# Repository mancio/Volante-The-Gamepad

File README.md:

# Volante-The-Gamepad
The new revolutionary joystick for car and flight simulation games.

*(Design still in progress 😆)*

&nbsp;

*carbon 3d preview*

&nbsp;

*3d preview with classic ABS box*

&nbsp;

*prototype with home-made touch buttons*

&nbsp;

&nbsp;

*prototype with classic RC remote buttons*

### Software 
The code is written by using the famous libray ```Joystick.h```. You can find some sketches still in testing [here](https://github.com/mancio/Volante-The-Gamepad/tree/master/Volante%20sketch).
After some tests seem that only the ```JOYSTICK_TYPE_JOYSTICK``` configuration works. Unfortunately Microsoft stop to support the HID human interface and only the basic function works. Still no solution for force feedback and particular multiaxis joystick.... now the more complex gaming simulation devices have their own drivers. You don't need the basic plug and play driver. Please have a look for the [HID architecture](https://docs.microsoft.com/en-us/windows-hardware/drivers/hid/) to understand and maybe help 😵

### Hardware
The hardware include a joystick case, buttons, knobs, the [Arduino Pro Micro](https://www.sparkfun.com/products/12640) and the the shield to interface the Arduino with the gamepad hw. The button pad modules and the shield boards are designed with [KiCad](http://kicad-pcb.org/). You can find on [OSH Park](https://oshpark.com) the PCBs ready to print.
1. [First design - only push buttons](https://oshpark.com/shared_projects/Fl5pqxbd)
2. [Second design - esternal pull-up resistors](https://oshpark.com/shared_projects/2LW72doK)

### Directory structure
1. [ArduinoJoystickLibrary-master](https://github.com/mancio/Volante-The-Gamepad/tree/master/ArduinoJoystickLibrary-master) - the Joystick library written by [Matthew Heironimus](https://github.com/MHeironimus)

2. [Fritzing](https://github.com/mancio/Volante-The-Gamepad/tree/master/Fritzing) - The Fritzing project with a prototype on breadbord. A small sketch to give a basic idea.

3. [Picture](https://github.com/mancio/Volante-The-Gamepad/tree/master/Picture) - some pictures for the Fritzing design project and the building process

4. [Volante sketch](https://github.com/mancio/Volante-The-Gamepad/tree/master/Volante%20sketch) - the code
   
   - [Volante](https://github.com/mancio/Volante-The-Gamepad/blob/master/Volante%20sketch/Volante/Volante.ino) - the main Arduino sketch. The sketch is design to be used with touch, capacitive and push buttons. The I/O pin can be in PULL-UP, PULL-DOWN or FLOAT configuration. 
      - touch button design: The PINs change to LOW when the finger or any not-hi-resistance organic object connect both the pad tracks. The finger and each resistor on the shield should be considered part of a voltage devider. Your dry skin should have an internal resistance of 2 MOhm so the resistors on the shield should be >= 10 MOhm. You can use [this](http://www.ohmslawcalculator.com/voltage-divider-calculator) voltage devider calculator to calculate the resistor value. The Arduino pin mosfets are LOW state when the input is about <= 2.5V. If you use a less conductive material to close the contacts of the pad maybe you will have to raise the resistance up to 20MOhm. Remeber that an high resistance voltage devider make the input *(dancing* 🎶 *)*. You could see the button blipping when you touch the button pad (only one contact or both). This effect is usualy caused by the power supply cord (I'm testing on a laptop). To reduce this effect you should a cercamic capacitor between the input and the ground. The capacitor store a small charge when you press the button and release it very slowly due to the very high value resistors. This stop the flipping but introduce a small delay. You should try some caps between 100pF (101 value) - 100nF (104 value) until your find the best compromise for your application. I suggest 10nF (103 value) capacitor.
      
      [Here](https://www.tinkercad.com/things/0KRsWQPfhxv) Some experiments on ThinkerCad.
      
      &nbsp;
      
      *touch button pad (the resistors are on the shield)* 
      &nbsp;
      
      - capacitive design: you can use the [TTP223](https://infusionsystems.com/support/TTP223.pdf) touch module as push button Normally LOW. The button switch on/off by using an internal timer that estimate the change of the capacitive charge during a fixed time slice. I suggest this configuration only for fast operation where is not required precision. The buttons are fast to trigger but sensible to external environment (high probability of fake positive) and the chip autoreset after few seconds (do not use as acceleretor button in a game)  
      
      &nbsp;
      
      *capacitive module* 
      &nbsp;
      
      - classic push button design: you can set up NO (normally open push button) using a pull-up configuration to reduce bouncing effects. When you push the button the pin will be GND. This is the most simple configuration, the button will be very reactive but harder to trigger (the most of NO push buttons are hard to click)
      
      &nbsp;
      
      *NO Momentary push button for RC* 
      &nbsp;

   - [test](https://github.com/mancio/Volante-The-Gamepad/blob/master/Volante%20sketch/test/test.ino) - Used to check the buttons assignment. 
   
      - int wiring[18] = Arduino pin in the IDE
      - int binding[18] = Buttons of joystick lib
      - String pull_mask[18] = pin state? High Low float (depending by the button type used)
      - analog_mask[18] = is analog? (for example pot is analog and push button is digital)
      
      Write the button structure with arrays here, execute the code and check in the table if the button binding is correct. If the binding satisfy your magic fingers copy this configuration to the main code ``Volante.ino``

5. [kicad](https://github.com/mancio/Volante-The-Gamepad/tree/master/kicad) - the Kicad scheme and PCB project.

   - [buttons_layout](https://github.com/mancio/Volante-The-Gamepad/tree/master/kicad/buttons_layout) - the blueprint of the gamepad case with RC push buttons
   
   - [buttons_layout_touch](https://github.com/mancio/Volante-The-Gamepad/tree/master/kicad/buttons_layout_touch) - the blueprint of the gamepad case with touch buttons
   
   - [lib](https://github.com/mancio/Volante-The-Gamepad/tree/master/kicad/lib) - kicad libraries of this project (include in kicad before open the project)
   
   - [shield](https://github.com/mancio/Volante-The-Gamepad/tree/master/kicad/shield) - firrst shield design only for capacitive and push buttons
   
      &nbsp;
      
      *First PCB printed by OSH Park* 
      &nbsp;
      
      &nbsp;
      
      *First PCB 3D view design by KiCad* 
      &nbsp;
   
   - [shield_touch](https://github.com/mancio/Volante-The-Gamepad/tree/master/kicad/shield_touch) - second shield design with extaernal pull-up resistor for push, capacitive and touch buttons.
   
      &nbsp;
      
      *Second PCB printed by OSH Park and assembled manually* 
      &nbsp;
      
      &nbsp;
      
      *Second PCB 3D view design by KiCad* 
      &nbsp;
   
   - [touch_button_fancy](https://github.com/mancio/Volante-The-Gamepad/tree/master/kicad/touch_button_fancy) - alternative push button PCB design
   
   - [touch_button_simple](https://github.com/mancio/Volante-The-Gamepad/tree/master/kicad/touch_button_simple) - main push button PCB design

6. [Assetto Corsa/Lotus GT Dream](https://github.com/mancio/Volante-The-Gamepad/tree/master/Assetto%20Corsa/Lotus%20GT%20Dream) - See *Cars for Assetto Corsa*

7. [Gamepad 3d design](https://github.com/mancio/Volante-The-Gamepad/tree/master/Gamepad%203d%20design) - 3d model of the gamepad Volante

      &nbsp;
      
      *3D rendering plastic box* 
      &nbsp;
   
### Game Setup

How to set up the Volante for a Awesome gaming experience

1. [Assetto corsa](https://www.assettocorsa.net/en/)

   &nbsp;
   
   *Main control configuration* 
   &nbsp;
   
   &nbsp;
   
   *Steering settings* 
   &nbsp;
   
### Cars for Assetto Corsa

To make the life easy to all the funs of the amazing game Assetto Corsa I decided to build my own cars (big tail and stick to the ground :red_car:). In the folder you find the game data and the blend file made with [blender](https://www.blender.org/)

1. [Lotus GT Dream](https://github.com/mancio/Volante-The-Gamepad/tree/master/Assetto%20Corsa/Lotus%20GT%20Dream)
   
### Facebook

You can find my project on Facebook on [Andrea Mancini's Machines](https://www.facebook.com/pg/mancio.tech/photos/?tab=album&album_id=2003051576403796)

### Conclusion
This project is focused to design a new kind of joystick that make pleasant the racing and flight simulation gaming experience.
The joystick will provide a slider linear potentiometer (throttle/brake), two knobs potentiometers (up/down - left/right) and 15 buttons
The innovation from the past consist in the _linear potentiometers_ that give the possibility to the player to perform absolutely precise movements.

#### Note
Don't worry if is not totally clear.... This project is still under development.

&nbsp;

#### Donation

Studying, designing and prototiping is expensive. If you believe in my project you can help me 😜 💲💲💲💲💲💲 😎

   - Bitcoin ```1KB6oxVrh5P6SbwFdtNHSG1rqPmdsaTaDV```

   - ETH ```0x7a5b81b2174748d6573a9ebf6b16d07c634c3e4f```

   - Litecoin ```LdVFaYbAsx9txhjVk1KURWvXqpVFDyT35k```

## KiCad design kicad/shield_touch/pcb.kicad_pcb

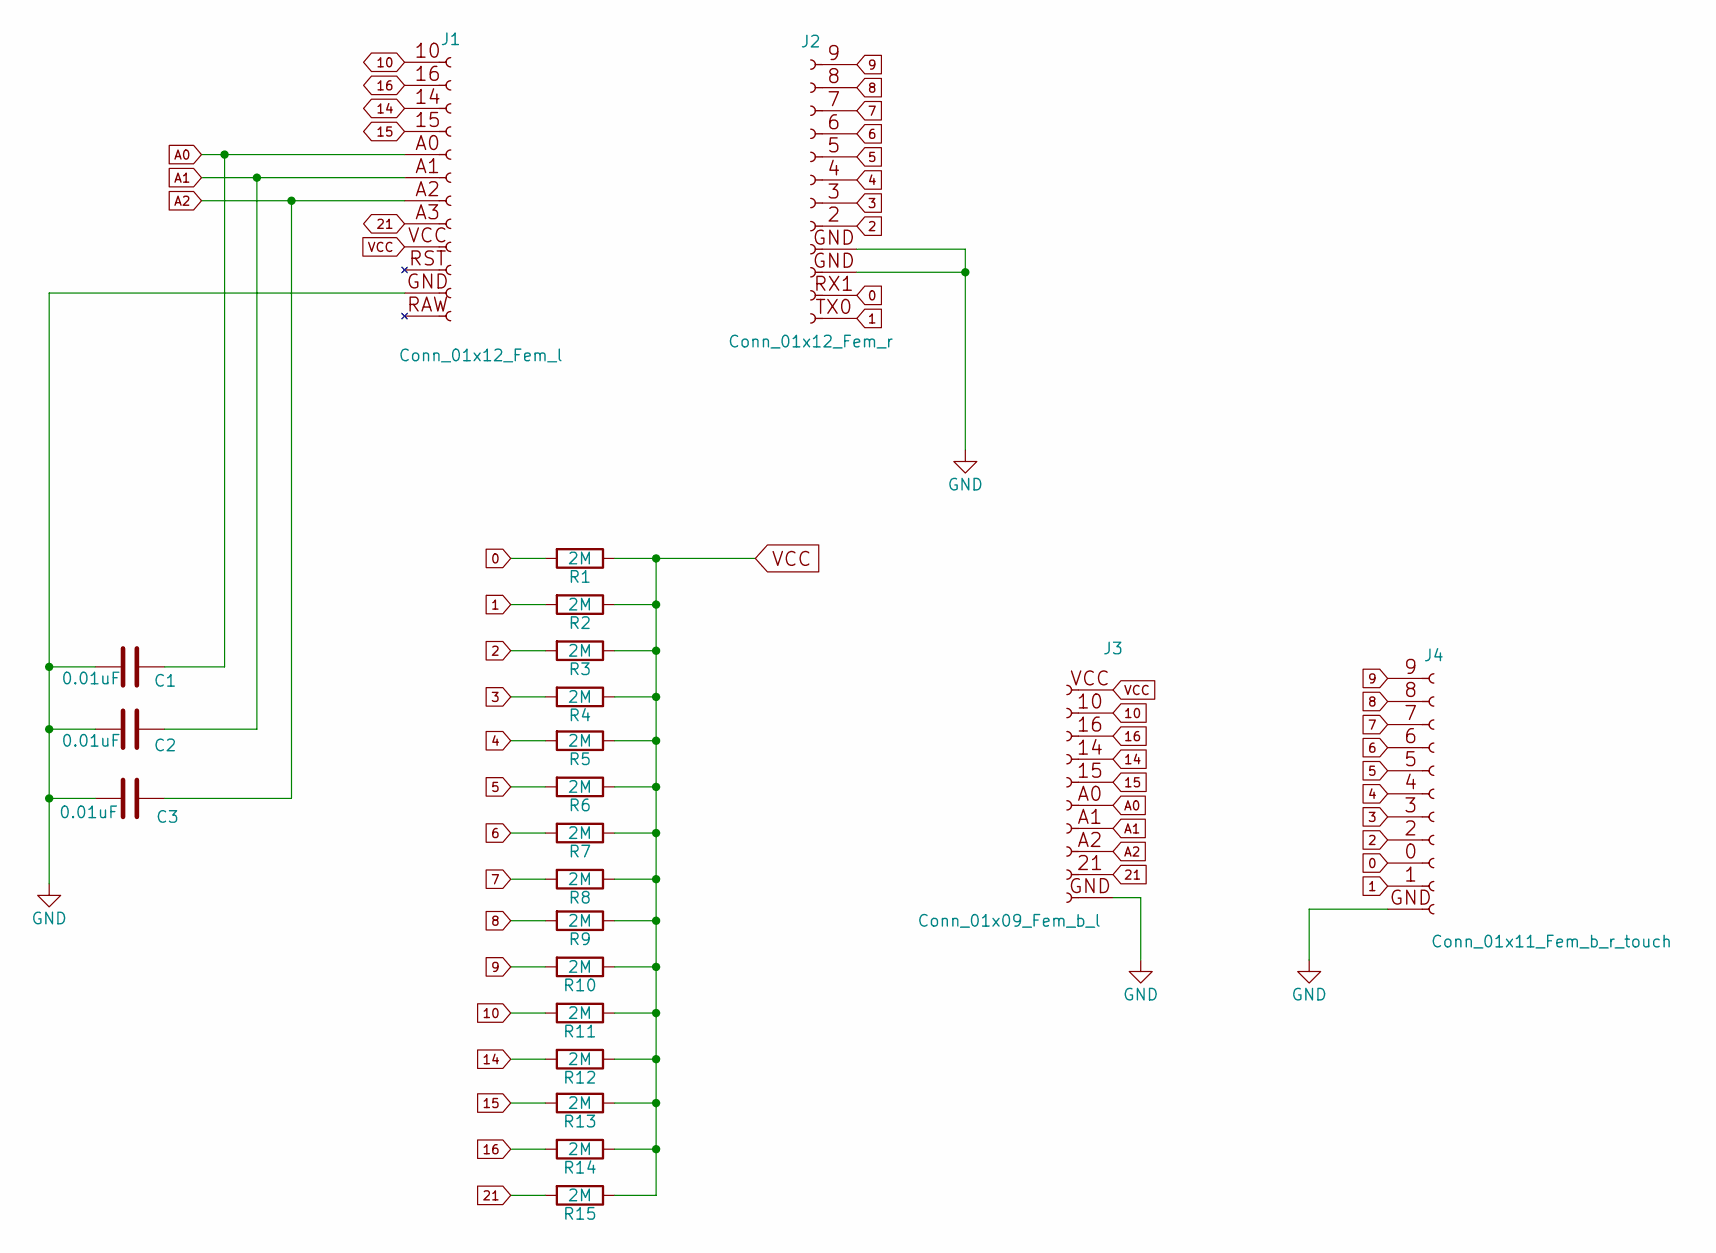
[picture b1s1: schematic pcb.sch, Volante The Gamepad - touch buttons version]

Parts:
C1, C2, C3: 0.01uF; C_Disc_D5.0mm_W2.5mm_P2.50mm
J1: Conn_01x12_Fem_l; SL-112-X-XX_1x12
J2: Conn_01x12_Fem_r; SL-112-X-XX_1x12
J3: Conn_01x09_Fem_b_l; SL-110-X-XX_1x10
J4: Conn_01x11_Fem_b_r_touch; SL-111-X-XX_1x11
R1, R2, R3, R4, R5, R6, R7, R8, R9, R10, R11, R12, R13, R14, R15: 2M; R_Axial_DIN0204_L3.6mm_D1.6mm_P2.54mm_Vertical

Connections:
0: J2.11, J4.9, R1.2
1: J2.12, J4.10, R2.2
2: J2.8, J4.8, R3.2
3: J2.7, J4.7, R4.2
4: J2.6, J4.6, R5.2
5: J2.5, J4.5, R6.2
6: J2.4, J4.4, R7.2
7: J2.3, J4.3, R8.2
8: J2.2, J4.2, R9.2
9: J2.1, J4.1, R10.2
10: J1.1, J3.2, R11.2
14: J1.3, J3.4, R12.2
15: J1.4, J3.5, R13.2
16: J1.2, J3.3, R14.2
21: J1.8, J3.9, R15.2
A0: C1.1, J1.5, J3.6
A1: C2.1, J1.6, J3.7
A2: C3.1, J1.7, J3.8
GND: C1.2, C2.2, C3.2, J1.11, J2.9, J2.10, J3.10, J4.11
VCC: J1.9, J3.1, R1.1, R2.1, R3.1, R4.1, R5.1, R6.1, R7.1, R8.1, R9.1, R10.1, R11.1, R12.1, R13.1, R14.1, R15.1

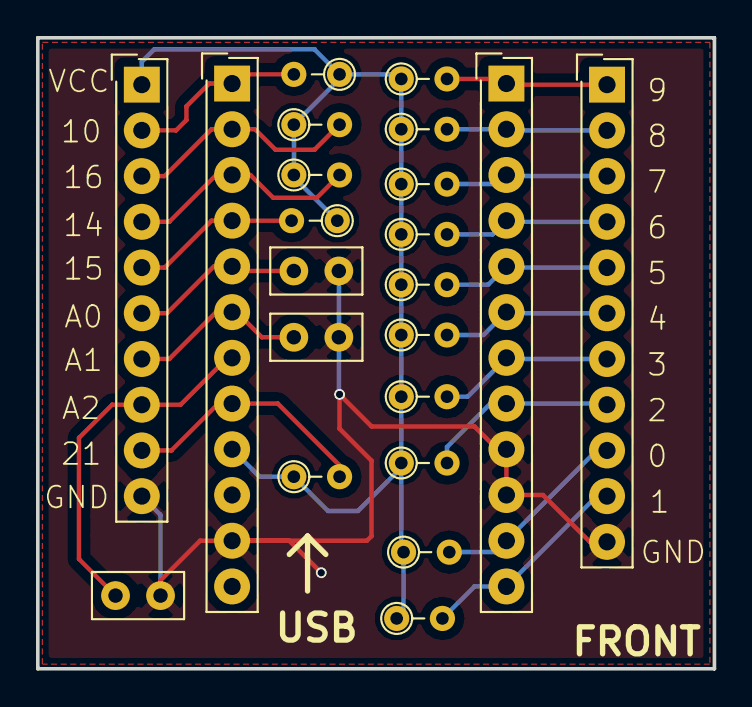
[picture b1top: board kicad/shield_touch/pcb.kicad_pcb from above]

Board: 2 copper layers, 37.6 x 35.1 mm, 22 parts (0 on the bottom side), 20 nets.

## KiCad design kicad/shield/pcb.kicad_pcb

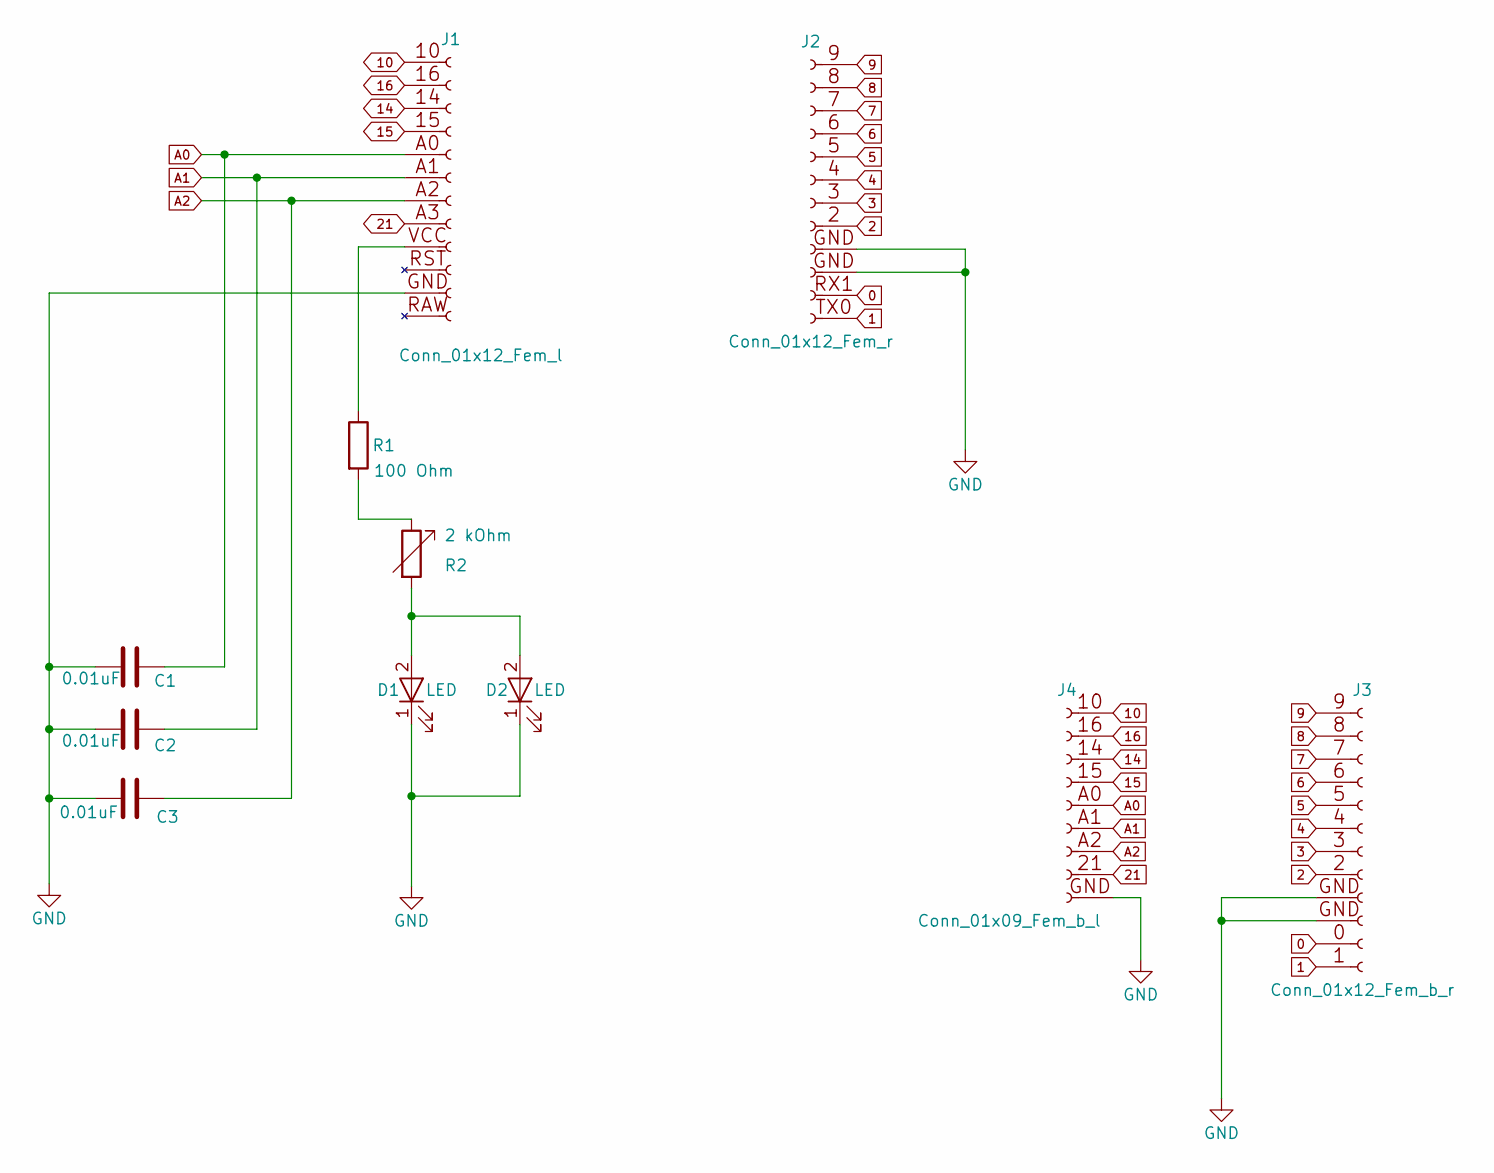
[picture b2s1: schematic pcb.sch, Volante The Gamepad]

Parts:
C1, C2, C3: 0.01uF; C_Disc_D5.0mm_W2.5mm_P2.50mm
D1, D2: LED; LED_D5.0mm
J1: Conn_01x12_Fem_l; SL-112-X-XX_1x12
J2: Conn_01x12_Fem_r; SL-112-X-XX_1x12
J3: Conn_01x12_Fem_b_r; SL-112-X-XX_1x12
J4: Conn_01x09_Fem_b_l; SL-109-X-XX_1x09
R1: 100 Ohm; R_Axial_DIN0207_L6.3mm_D2.5mm_P10.16mm_Horizontal
R2: 2 kOhm; Potentiometer_Triwood_RM-065

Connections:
0: J2.11, J3.11
1: J2.12, J3.12
2: J2.8, J3.8
3: J2.7, J3.7
4: J2.6, J3.6
5: J2.5, J3.5
6: J2.4, J3.4
7: J2.3, J3.3
8: J2.2, J3.2
9: J2.1, J3.1
10: J1.1, J4.1
14: J1.3, J4.3
15: J1.4, J4.4
16: J1.2, J4.2
21: J1.8, J4.8
A0: C1.1, J1.5, J4.5
A1: C2.1, J1.6, J4.6
A2: C3.1, J1.7, J4.7
GND: C1.2, C2.2, C3.2, D1.1 (K), D2.1 (K), J1.11, J2.9, J2.10, J3.9, J3.10, J4.9
unnamed: D1.2 (A), D2.2 (A), R2.2
unnamed: J1.9, R1.1
unnamed: R1.2, R2.1

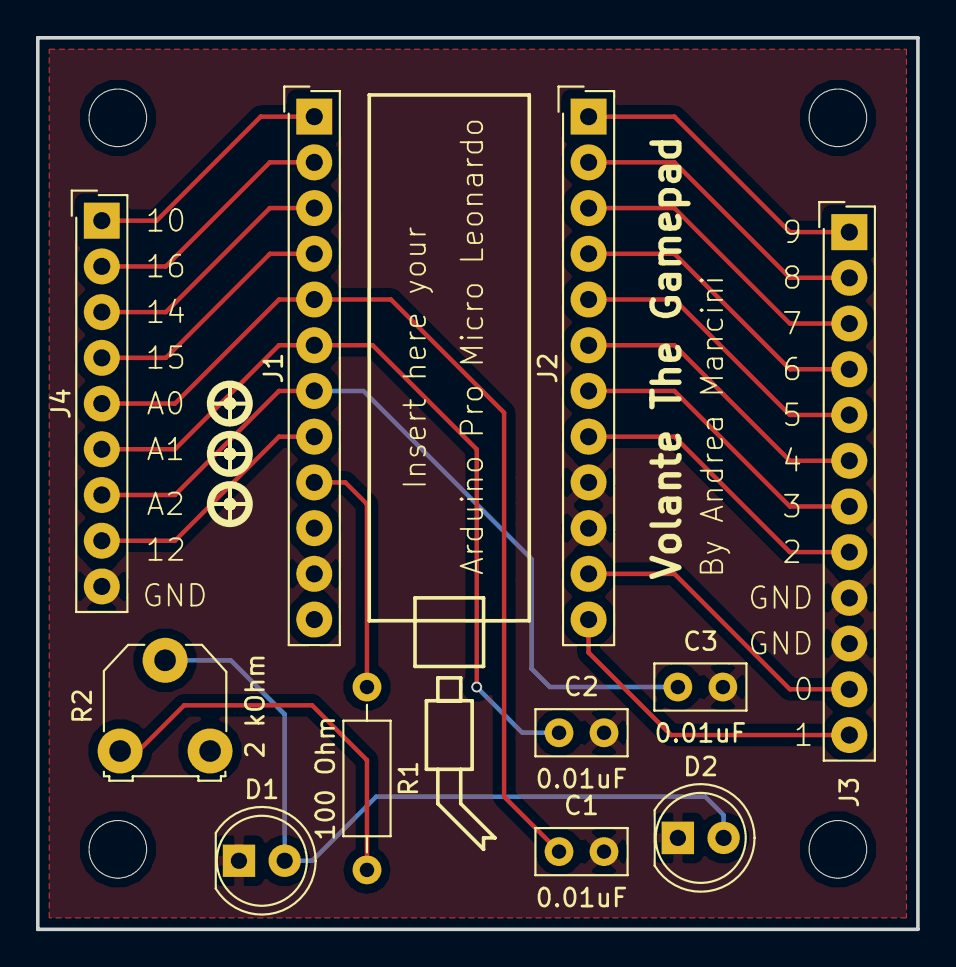
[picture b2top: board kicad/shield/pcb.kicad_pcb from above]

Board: 2 copper layers, 48.9 x 49.5 mm, 11 parts (0 on the bottom side), 22 nets.

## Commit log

2018-02-13 Add files via upload
    First commit still testing
2018-02-13 Update README.md
    presentation
2018-02-13 commit prova
    commit prova
2018-02-13 pcb finshed
    13/02/2018
2018-02-15 update
    - verify arduino socket dimension
    - change port 12 to 21
    - disable TXLED and RXLED
2018-02-16 maybe final
    - ultimate PCB design
    - add potentiometer for led control
    - checked connections
2018-02-17 update
    - check pcb errors
    - example of BOM (not for this board)
    - BOM still TODO
2018-02-17 updates
    - print the front and back copper layer to check the connections
    - add silks pictures
    - ready to print first prototype
2018-02-19 update
    - layout in pdf
    - moved slider on the left
    - moved pin test
2018-02-19 update
    - link to OSHPark
2018-02-22 update
    - fix the code sizeof is not a for..... :)
2018-02-22 update
    - fix the code SPI pins can be used as digital input but they need an external 10K pull-up resistor
2018-02-28 update
    - fix the code
    - SPI ports working (the problem was the GND wire unsoldered)
    - all buttons are working
2018-04-16 capacitive buttons
    - to fix
2018-04-16 update
    - now works
2018-05-14 prova
    prova
2018-05-14 prova
2018-05-16 update
    - still to fix a lot of stuff
2018-05-19 update
    - still to fix
2018-05-19 update
    - still working
2018-05-19 update
    - drc report
2018-05-20 update
    - almost finished
2018-05-21 update
    - drawing buttons
    - still to finish
2018-05-22 update
    - try to make a better button
2018-05-23 update
    - try to make several button layouts
2018-05-24 update
    - import my_lib
2018-06-03 update
    - designing pcb with vertical resistors
2018-06-03 update
    - pcb complete and tested
2018-06-05 update
    - resistors on front side pcb
2018-06-06 update
    - pcb design pictures
2018-06-06 update
    - try to make a hole touch button... mah :-1:
2018-06-08 update
    - fix pcb
2018-06-08 touch button mask layout
2018-06-08 VCC pin
    - add Vcc pin
2018-06-18 added throught via
    - added throught via to increase GND contacts
2018-06-18 added logos
    - open hw logo
    - front back logos
2018-06-18 change sch and pcb page settings
    - details
    - data
    - title
2018-07-10 not used
2018-07-10 update
    more info
2018-07-11 TTP223
2018-12-16 update
    better touch button pad
